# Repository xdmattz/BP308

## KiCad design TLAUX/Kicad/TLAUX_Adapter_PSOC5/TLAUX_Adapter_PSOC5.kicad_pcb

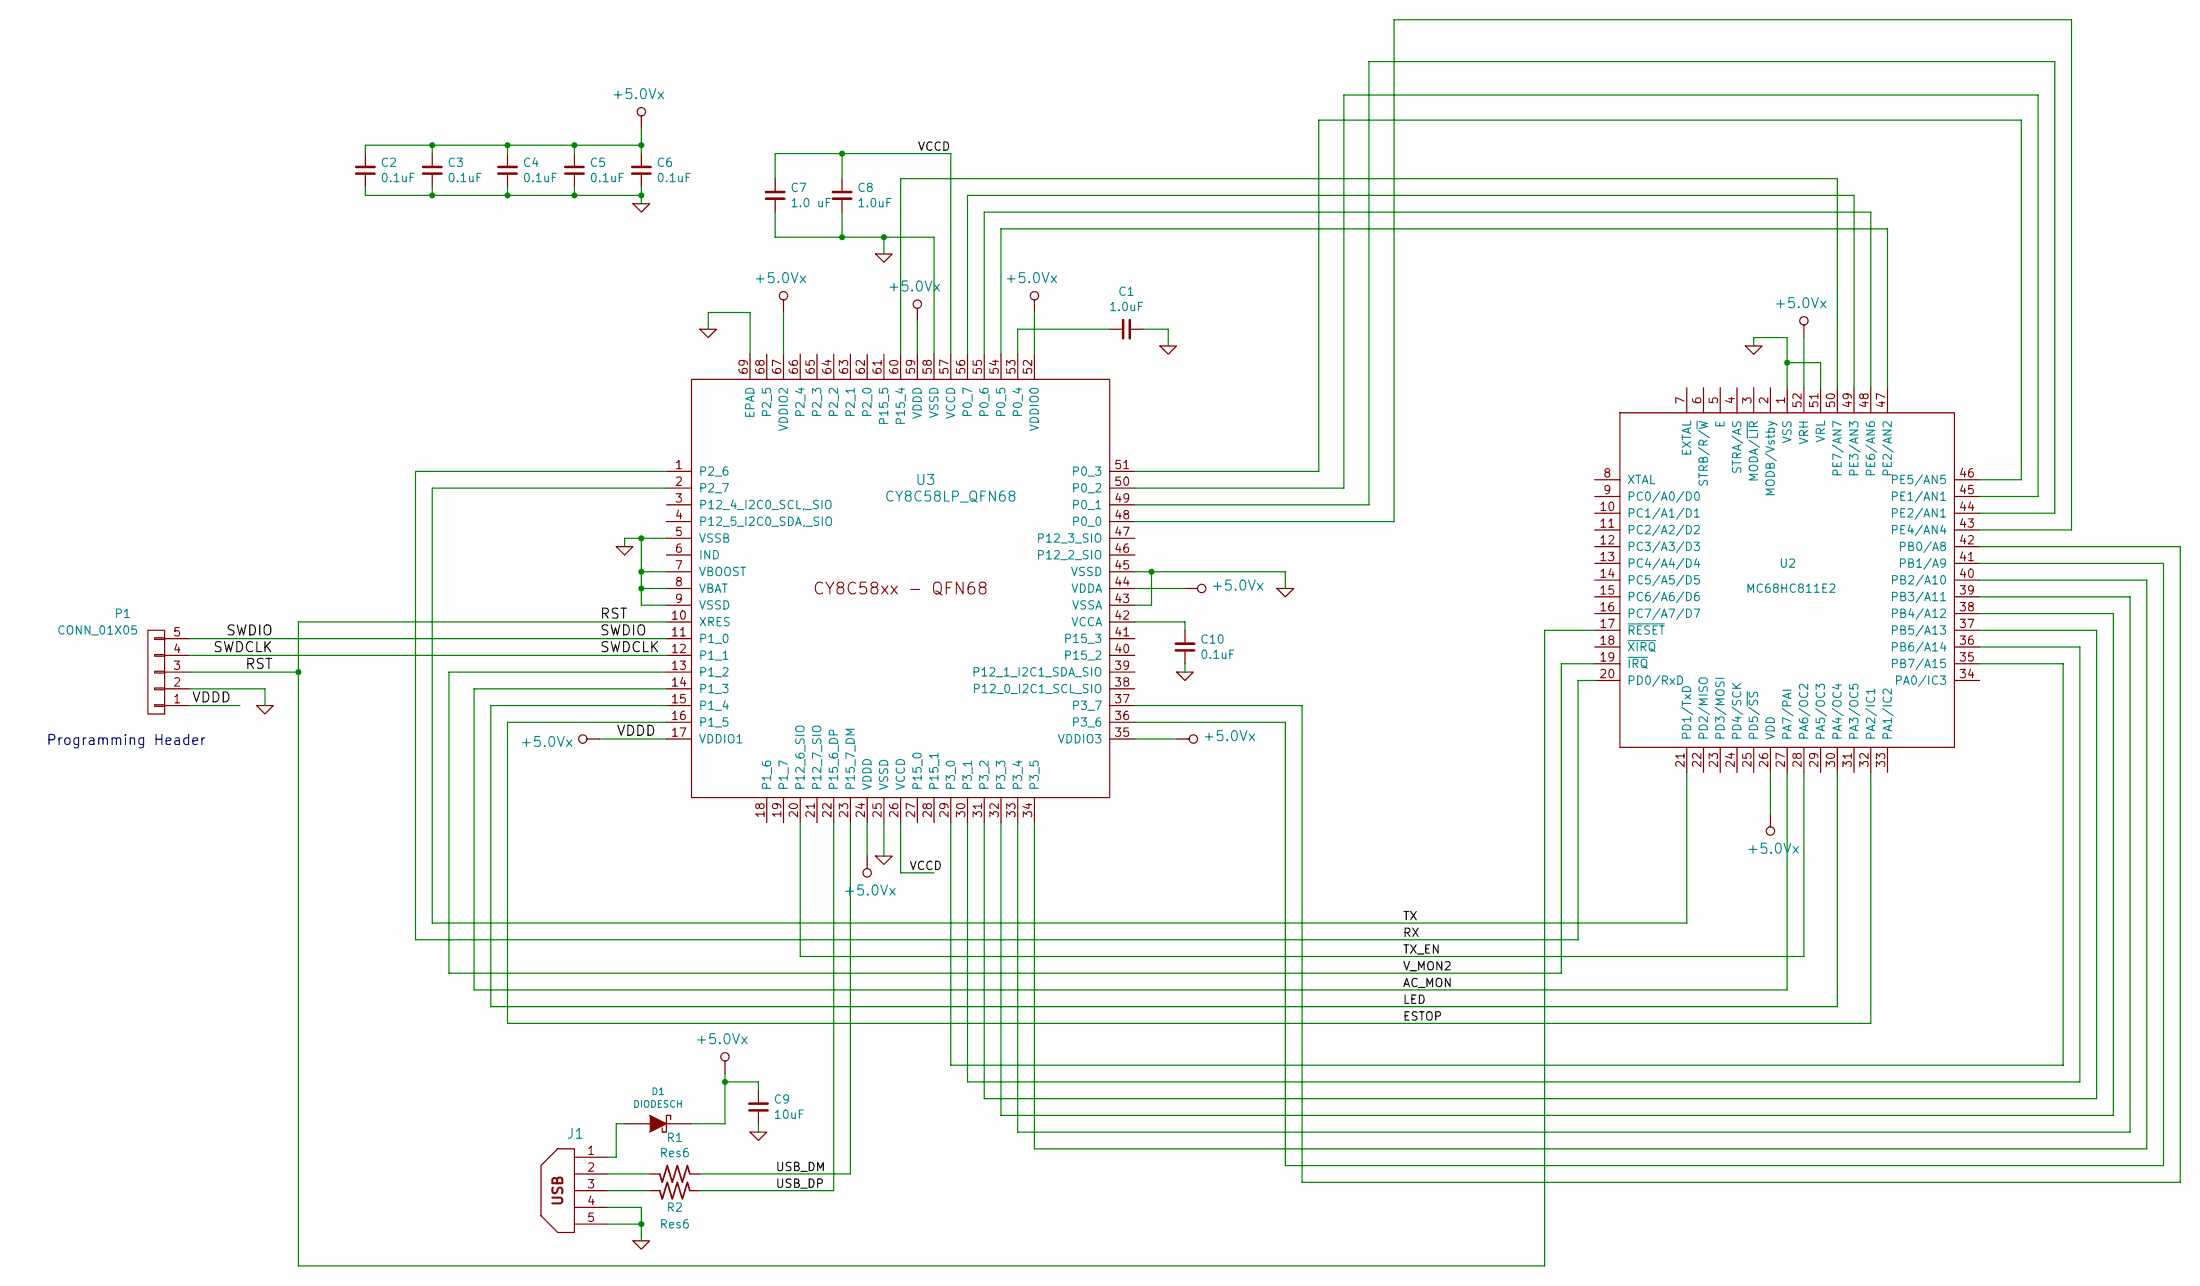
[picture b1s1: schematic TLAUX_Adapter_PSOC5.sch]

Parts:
C1, C8: 1.0uF; cap_0603
C2, C3, C4, C5, C6, C10: 0.1uF; cap_0402
C7: 1.0 uF; cap_0603
C9: 10uF; cap_0805
D1: DIODESCH; SOD-123
J1: USB_micro-B; conn_usb_B_mini_smd
P1: CONN_01X05; pin_strip_5
R1, R2: Res6; res_0603
U2: MC68HC811E2; PLCC_52_Socket
U3: CY8C58LP_QFN68; QFN_68; Digikey 428-3231-ND

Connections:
+5.0Vx: C2.2, C3.2, C4.2, C5.2, C6.2, C9.2, D1.1 (K), P1.1, U2.26 (VDD), U2.52 (VRH), U3.17 (VDDIO1), U3.24 (VDDD), U3.35 (VDDIO3), U3.44 (VDDA), U3.52 (VDDIO0), U3.59 (VDDD), U3.67 (VDDIO2)
/AC_MON: U2.27 (PA7/PAI), U3.14 (P1_3)
/ESTOP: U2.32 (PA2/IC1), U3.16 (P1_5)
/LED: U2.30 (PA4/OC4), U3.15 (P1_4)
/RST: P1.3, U2.17 (~RESET), U3.10 (XRES)
/RX: U2.20 (PD0/RxD), U3.1 (P2_6)
/SWDCLK: P1.4, U3.12 (P1_1)
/SWDIO: P1.5, U3.11 (P1_0)
/TX: U2.21 (PD1/TxD), U3.2 (P2_7)
/TX_EN: U2.28 (PA6/OC2), U3.20 (P12_6_SIO)
/USB_DM: R1.1, U3.23 (P15_7_DM)
/USB_DP: R2.1, U3.22 (P15_6_DP)
/VCCD: C7.2, C8.2, U3.26 (VCCD), U3.57 (VCCD)
/V_MON2: U2.19 (~IRQ), U3.13 (P1_2)
GND: C1.1, C2.1, C3.1, C4.1, C5.1, C6.1, C7.1, C8.1, C9.1, C10.1, J1.4, J1.5, P1.2, U2.1 (VSS), U2.51 (VRL), U3.5 (VSSB), U3.7 (VBOOST), U3.8 (VBAT), U3.9 (VSSD), U3.25 (VSSD), U3.43 (VSSA), U3.45 (VSSD), U3.58 (VSSD), U3.69 (EPAD)
unnamed: C1.2, U3.53 (P0_4)
unnamed: C10.2, U3.42 (VCCA)
unnamed: D1.2 (A), J1.1
unnamed: J1.2, R1.2
unnamed: J1.3, R2.2
unnamed: U2.35 (PB7/A15), U3.29 (P3_0)
unnamed: U2.36 (PB6/A14), U3.30 (P3_1)
unnamed: U2.37 (PB5/A13), U3.31 (P3_2)
unnamed: U2.38 (PB4/A12), U3.32 (P3_3)
unnamed: U2.39 (PB3/A11), U3.33 (P3_4)
unnamed: U2.40 (PB2/A10), U3.34 (P3_5)
unnamed: U2.41 (PB1/A9), U3.36 (P3_6)
unnamed: U2.42 (PB0/A8), U3.37 (P3_7)
unnamed: U2.43 (PE4/AN4), U3.48 (P0_0)
unnamed: U2.44 (PE2/AN1), U3.49 (P0_1)
unnamed: U2.45 (PE1/AN1), U3.50 (P0_2)
unnamed: U2.46 (PE5/AN5), U3.51 (P0_3)
unnamed: U2.47 (PE2/AN2), U3.54 (P0_5)
unnamed: U2.48 (PE6/AN6), U3.55 (P0_6)
unnamed: U2.49 (PE3/AN3), U3.56 (P0_7)
unnamed: U2.50 (PE7/AN7), U3.60 (P15_4)

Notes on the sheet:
Programming Header

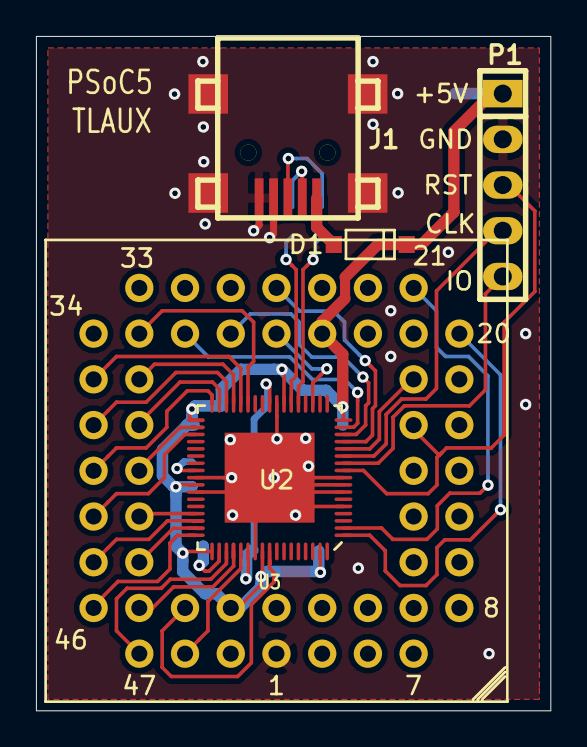
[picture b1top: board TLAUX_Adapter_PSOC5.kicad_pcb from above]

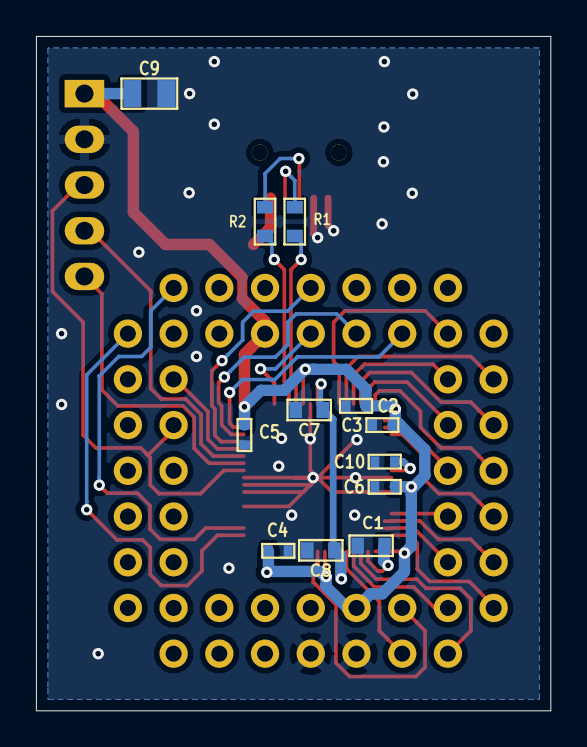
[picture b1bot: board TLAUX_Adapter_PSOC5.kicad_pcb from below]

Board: 2 copper layers, 28.6 x 37.5 mm, 17 parts (12 on the bottom side), 36 nets.

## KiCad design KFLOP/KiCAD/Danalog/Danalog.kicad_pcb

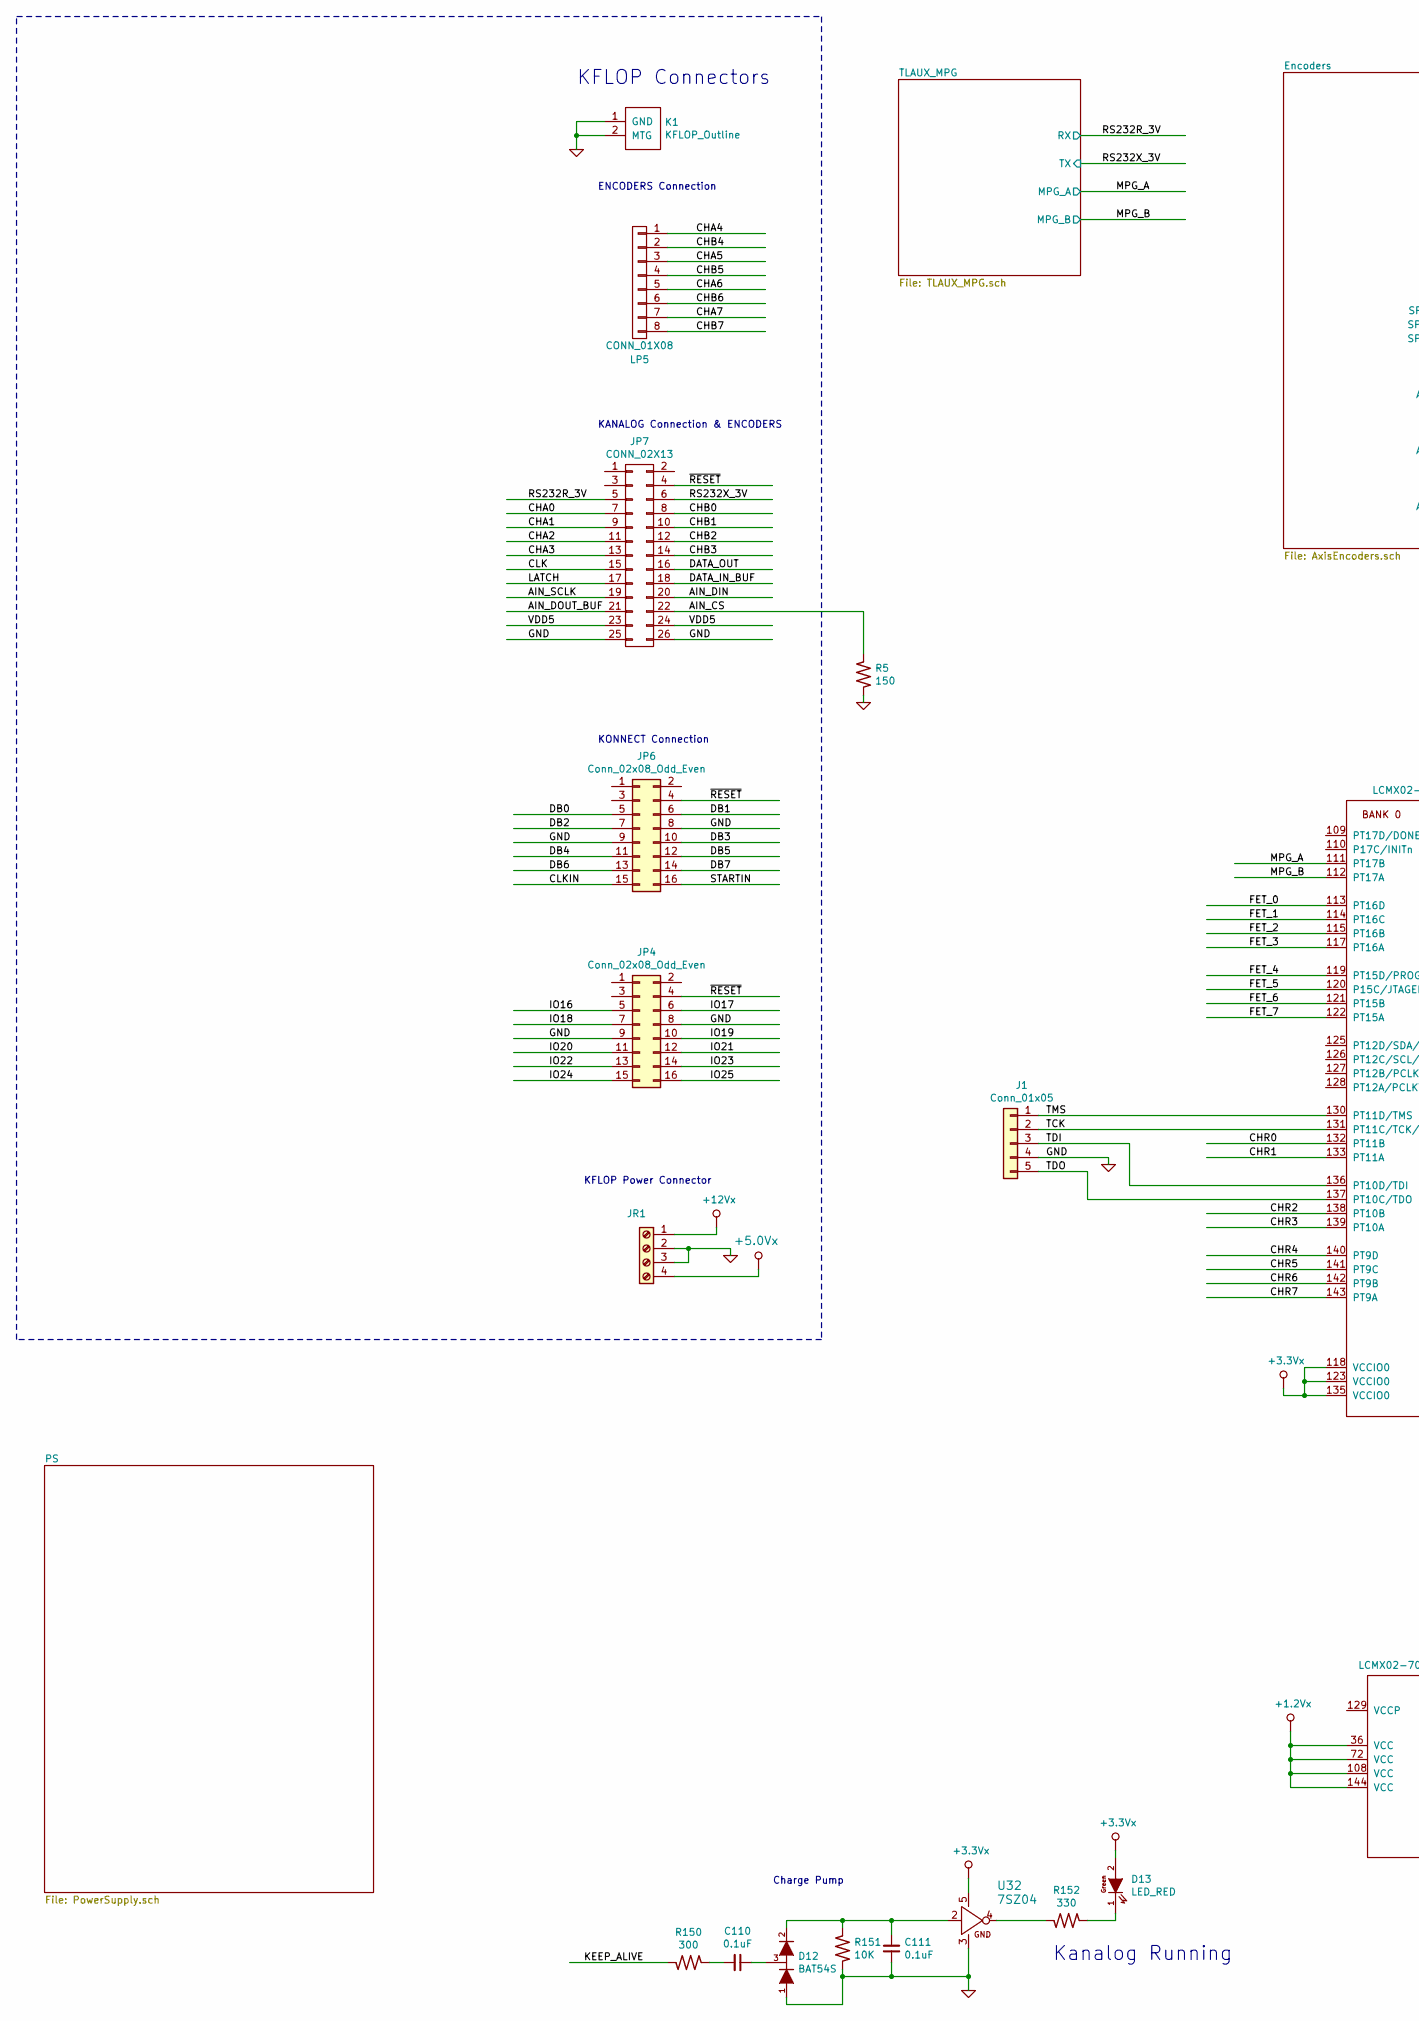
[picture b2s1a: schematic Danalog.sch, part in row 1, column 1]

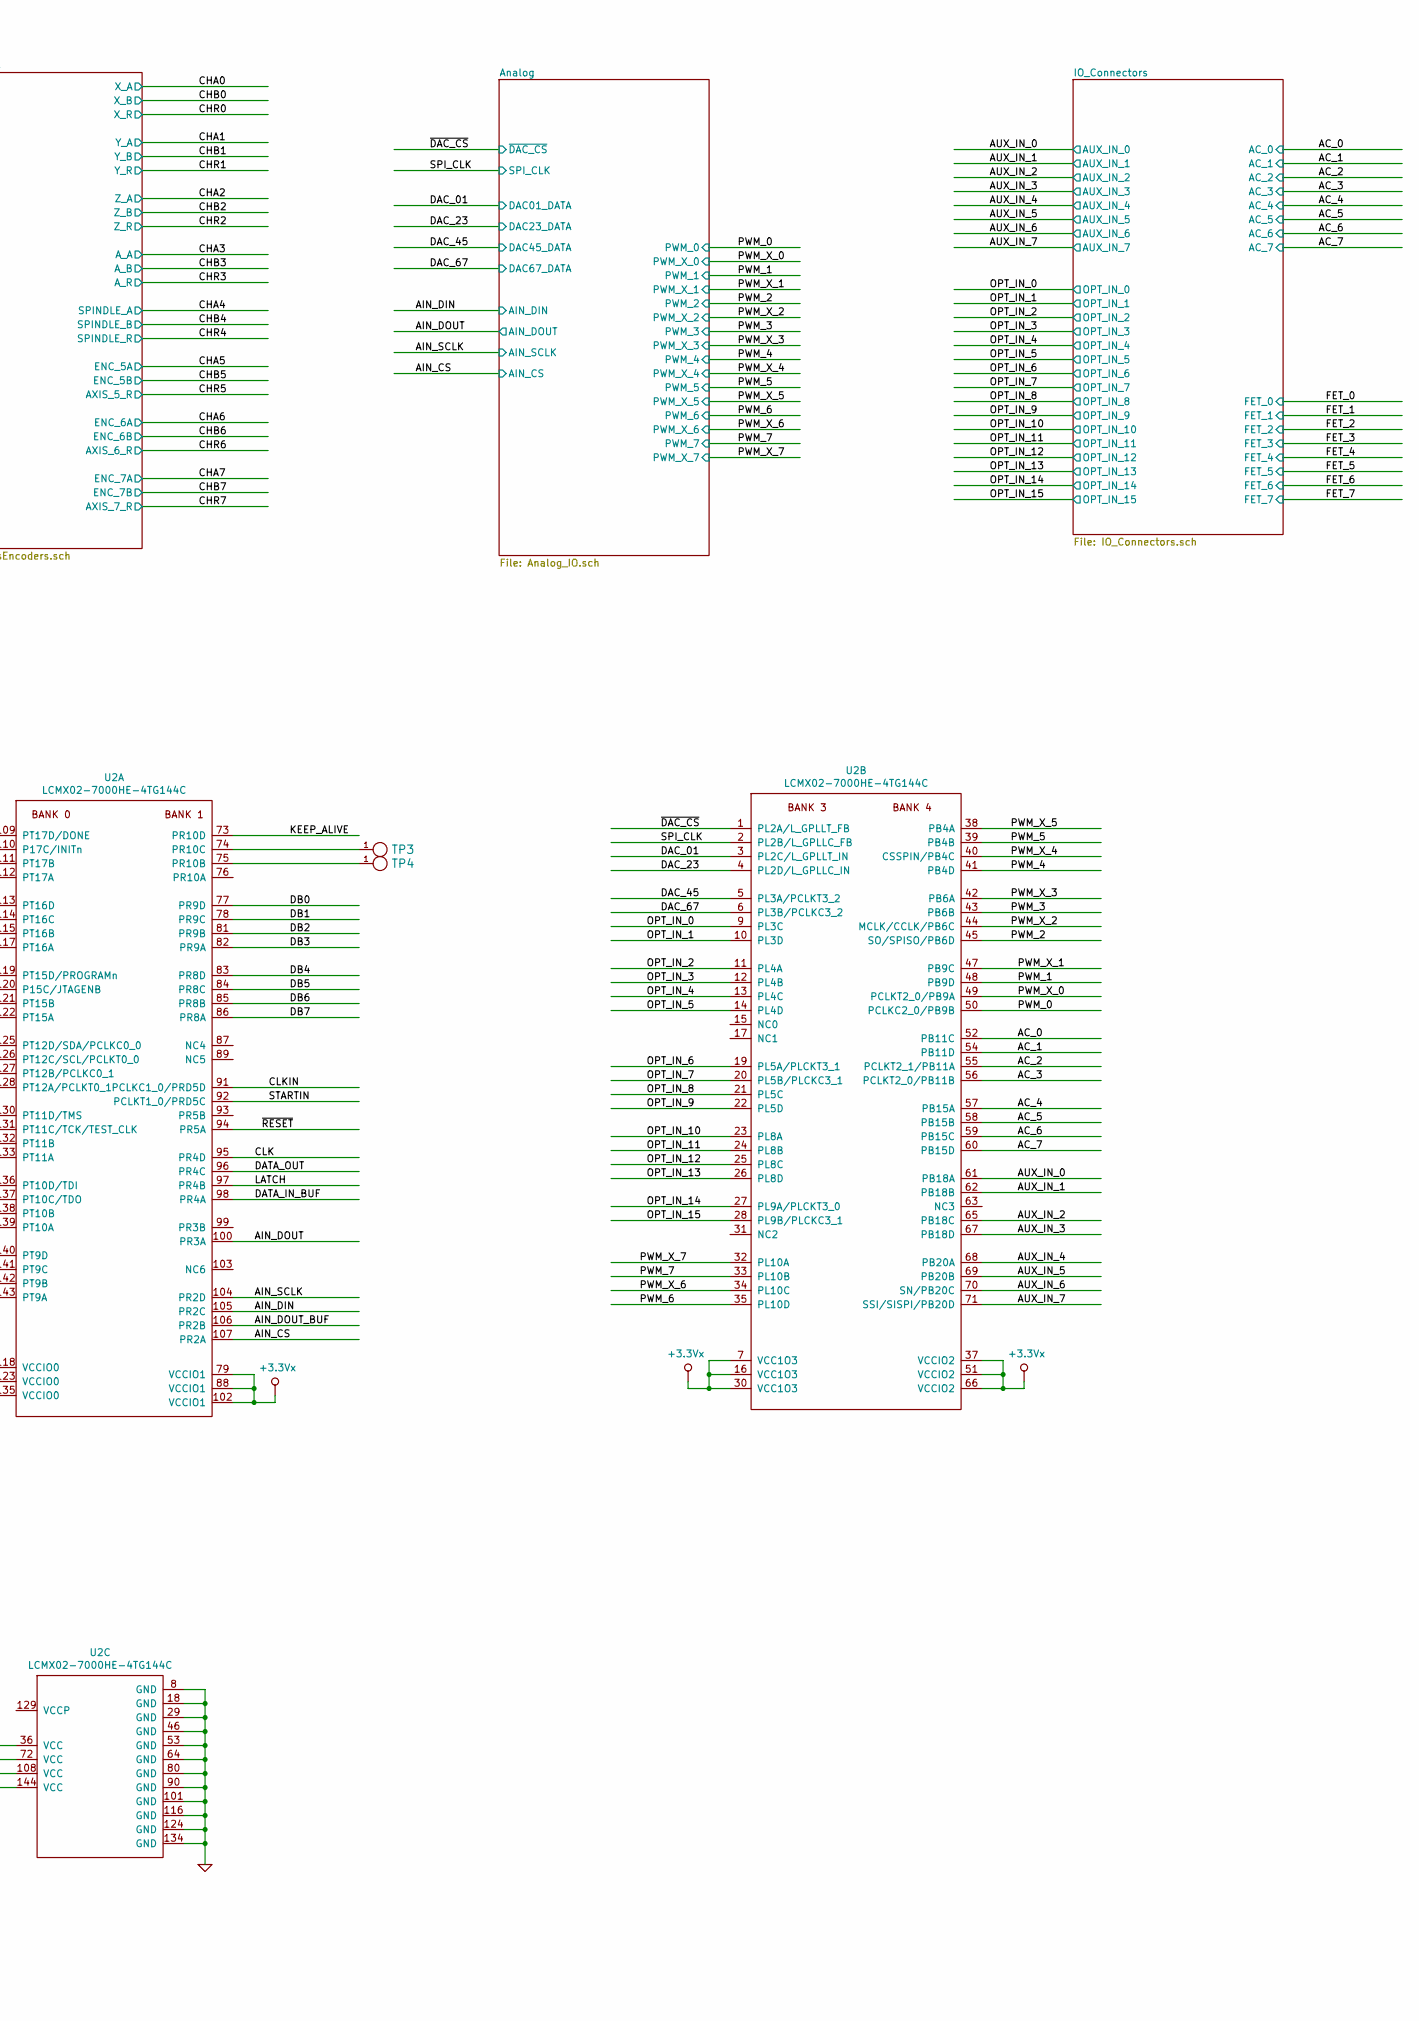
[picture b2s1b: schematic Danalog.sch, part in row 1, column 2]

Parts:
C110, C111: 0.1uF; cap_0603
D12: BAT54S; sot-23
D13: LED_RED; Led_1206_Short
J1: Conn_01x05; Header_5x100
JP4, JP6: Conn_02x08_Odd_Even; vasch_strip_8x2
JP7: CONN_02X13; vasch_strip_13x2
JR1: Screw_Terminal_01x04; Terminal_Block_RA_4_5_08mm
K1: KFLOP_Outline; KFLOP_Mounting
LP5: CONN_01X08; Molex_43860_rj45_no_shield
R5: 150; res_0805
R150: 300; res_0603
R151: 10K; res_0603
R152: 330; res_0603
TP3, TP4: TEST_POINT; TP60
U2: LCMX02-7000HE-4TG144C; QFP-144_20x20_Pitch0.5mm
U32: 7SZ04; sot-23-5

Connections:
+1.2Vx: U2.36 (VCC), U2.72 (VCC), U2.108 (VCC), U2.144 (VCC); also elsewhere on the board
+3.3Vx: D13.2 (A), U2.7 (VCC1O3), U2.16 (VCC1O3), U2.30 (VCC1O3), U2.37 (VCCIO2), U2.51 (VCCIO2), U2.66 (VCCIO2), U2.79 (VCCIO1), U2.88 (VCCIO1), U2.102 (VCCIO1), U2.118 (VCCIO0), U2.123 (VCCIO0), U2.135 (VCCIO0), U32.5 (VCC); also elsewhere on the board
+5.0Vx: JR1.4; also elsewhere on the board
+12Vx: JR1.1; also elsewhere on the board
/AC_0: U2.52 (PB11C); also elsewhere on the board
/AC_1: U2.54 (PB11D); also elsewhere on the board
/AC_2: U2.55 (PCLKT2_1/PB11A); also elsewhere on the board
/AC_3: U2.56 (PCLKT2_0/PB11B); also elsewhere on the board
/AC_4: U2.57 (PB15A); also elsewhere on the board
/AC_5: U2.58 (PB15B); also elsewhere on the board
/AC_6: U2.59 (PB15C); also elsewhere on the board
/AC_7: U2.60 (PB15D); also elsewhere on the board
/AIN_CS: JP7.22, R5.2, U2.107 (PR2A); also elsewhere on the board
/AIN_DIN: JP7.20, U2.105 (PR2C); also elsewhere on the board
/AIN_DOUT: U2.100 (PR3A); also elsewhere on the board
/AIN_DOUT_BUF: JP7.21, U2.106 (PR2B)
/AIN_SCLK: JP7.19, U2.104 (PR2D); also elsewhere on the board
/AUX_IN_0: U2.61 (PB18A); also elsewhere on the board
/AUX_IN_1: U2.62 (PB18B); also elsewhere on the board
/AUX_IN_2: U2.65 (PB18C); also elsewhere on the board
/AUX_IN_3: U2.67 (PB18D); also elsewhere on the board
/AUX_IN_4: U2.68 (PB20A); also elsewhere on the board
/AUX_IN_5: U2.69 (PB20B); also elsewhere on the board
/AUX_IN_6: U2.70 (SN/PB20C); also elsewhere on the board
/AUX_IN_7: U2.71 (SSI/SISPI/PB20D); also elsewhere on the board
/CHA0: JP7.7; also elsewhere on the board
/CHA1: JP7.9; also elsewhere on the board
/CHA2: JP7.11; also elsewhere on the board
/CHA3: JP7.13; also elsewhere on the board
/CHA4: LP5.1; also elsewhere on the board
/CHA5: LP5.3; also elsewhere on the board
/CHA6: LP5.5; also elsewhere on the board
/CHA7: LP5.7; also elsewhere on the board
/CHB0: JP7.8; also elsewhere on the board
/CHB1: JP7.10; also elsewhere on the board
/CHB2: JP7.12; also elsewhere on the board
/CHB3: JP7.14; also elsewhere on the board
/CHB4: LP5.2; also elsewhere on the board
/CHB5: LP5.4; also elsewhere on the board
/CHB6: LP5.6; also elsewhere on the board
/CHB7: LP5.8; also elsewhere on the board
/CHR0: U2.132 (PT11B); also elsewhere on the board
/CHR1: U2.133 (PT11A); also elsewhere on the board
/CHR2: U2.138 (PT10B); also elsewhere on the board
/CHR3: U2.139 (PT10A); also elsewhere on the board
/CHR4: U2.140 (PT9D); also elsewhere on the board
/CHR5: U2.141 (PT9C); also elsewhere on the board
/CHR6: U2.142 (PT9B); also elsewhere on the board
/CHR7: U2.143 (PT9A); also elsewhere on the board
/CLK: JP7.15, U2.95 (PR4D)
/CLKIN: JP6.15, U2.91 (PCLKC1_0/PRD5D)
/DAC_01: U2.3 (PL2C/L_GPLLT_IN); also elsewhere on the board
/DAC_23: U2.4 (PL2D/L_GPLLC_IN); also elsewhere on the board
/DAC_45: U2.5 (PL3A/PCLKT3_2); also elsewhere on the board
/DAC_67: U2.6 (PL3B/PCLKC3_2); also elsewhere on the board
/DATA_IN_BUF: JP7.18, U2.98 (PR4A)
/DATA_OUT: JP7.16, U2.96 (PR4C)
/DB0: JP6.5, U2.77 (PR9D)
/DB1: JP6.6, U2.78 (PR9C)
/DB2: JP6.7, U2.81 (PR9B)
/DB3: JP6.10, U2.82 (PR9A)
/DB4: JP6.11, U2.83 (PR8D)
/DB5: JP6.12, U2.84 (PR8C)
/DB6: JP6.13, U2.85 (PR8B)
/DB7: JP6.14, U2.86 (PR8A)
/FET_0: U2.113 (PT16D); also elsewhere on the board
/FET_1: U2.114 (PT16C); also elsewhere on the board
/FET_2: U2.115 (PT16B); also elsewhere on the board
/FET_3: U2.117 (PT16A); also elsewhere on the board
/FET_4: U2.119 (PT15D/PROGRAMn); also elsewhere on the board
/FET_5: U2.120 (P15C/JTAGENB); also elsewhere on the board
/FET_6: U2.121 (PT15B); also elsewhere on the board
/FET_7: U2.122 (PT15A); also elsewhere on the board
/IO16: JP4.5
/IO17: JP4.6
/IO18: JP4.7
/IO19: JP4.10
/IO20: JP4.11
/IO21: JP4.12
/IO22: JP4.13
/IO23: JP4.14
/IO24: JP4.15
/IO25: JP4.16
/KEEP_ALIVE: R150.1, U2.73 (PR10D)
/LATCH: JP7.17, U2.97 (PR4B)
/MPG_A: U2.111 (PT17B); also elsewhere on the board
/MPG_B: U2.112 (PT17A); also elsewhere on the board
/OPT_IN_0: U2.9 (PL3C); also elsewhere on the board
/OPT_IN_1: U2.10 (PL3D); also elsewhere on the board
/OPT_IN_2: U2.11 (PL4A); also elsewhere on the board
/OPT_IN_3: U2.12 (PL4B); also elsewhere on the board
/OPT_IN_4: U2.13 (PL4C); also elsewhere on the board
/OPT_IN_5: U2.14 (PL4D); also elsewhere on the board
/OPT_IN_6: U2.19 (PL5A/PLCKT3_1); also elsewhere on the board
/OPT_IN_7: U2.20 (PL5B/PLCKC3_1); also elsewhere on the board
/OPT_IN_8: U2.21 (PL5C); also elsewhere on the board
/OPT_IN_9: U2.22 (PL5D); also elsewhere on the board
/OPT_IN_10: U2.23 (PL8A); also elsewhere on the board
/OPT_IN_11: U2.24 (PL8B); also elsewhere on the board
/OPT_IN_12: U2.25 (PL8C); also elsewhere on the board
/OPT_IN_13: U2.26 (PL8D); also elsewhere on the board
/OPT_IN_14: U2.27 (PL9A/PLCKT3_0); also elsewhere on the board
/OPT_IN_15: U2.28 (PL9B/PLCKC3_1); also elsewhere on the board
/PWM_0: U2.50 (PCLKC2_0/PB9B); also elsewhere on the board
/PWM_1: U2.48 (PB9D); also elsewhere on the board
/PWM_2: U2.45 (SO/SPISO/PB6D); also elsewhere on the board
/PWM_3: U2.43 (PB6B); also elsewhere on the board
/PWM_4: U2.41 (PB4D); also elsewhere on the board
/PWM_5: U2.39 (PB4B); also elsewhere on the board
/PWM_6: U2.35 (PL10D); also elsewhere on the board
/PWM_7: U2.33 (PL10B); also elsewhere on the board
/PWM_X_0: U2.49 (PCLKT2_0/PB9A); also elsewhere on the board
/PWM_X_1: U2.47 (PB9C); also elsewhere on the board
/PWM_X_2: U2.44 (MCLK/CCLK/PB6C); also elsewhere on the board
/PWM_X_3: U2.42 (PB6A); also elsewhere on the board
/PWM_X_4: U2.40 (CSSPIN/PB4C); also elsewhere on the board
/PWM_X_5: U2.38 (PB4A); also elsewhere on the board
/PWM_X_6: U2.34 (PL10C); also elsewhere on the board
/PWM_X_7: U2.32 (PL10A); also elsewhere on the board
/RS232R_3V: JP7.5; also elsewhere on the board
/RS232X_3V: JP7.6; also elsewhere on the board
/SPI_CLK: U2.2 (PL2B/L_GPLLC_FB); also elsewhere on the board
/STARTIN: JP6.16, U2.92 (PCLKT1_0/PRD5C)
/TCK: J1.2, U2.131 (PT11C/TCK/TEST_CLK)
/TDI: J1.3, U2.136 (PT10D/TDI)
/TDO: J1.5, U2.137 (PT10C/TDO)
/TMS: J1.1, U2.130 (PT11D/TMS)
/VDD5: JP7.23, JP7.24
/~DAC_CS: U2.1 (PL2A/L_GPLLT_FB); also elsewhere on the board
/~RESET: JP4.4, JP6.4, JP7.4, U2.94 (PR5A)
GND: C111.2, D12.1 (A1), J1.4, JP4.8, JP4.9, JP6.8, JP6.9, JP7.25, JP7.26, JR1.2, JR1.3, K1.1 (GND), K1.2 (MTG), R5.1, R151.2, U2.8 (GND), U2.18 (GND), U2.29 (GND), U2.46 (GND), U2.53 (GND), U2.64 (GND), U2.80 (GND), U2.90 (GND), U2.101 (GND), U2.116 (GND), U2.124 (GND), U2.134 (GND), U32.3 (GND); also elsewhere on the board
unnamed: C110.1, R150.2
unnamed: C110.2, D12.3 (KA)
unnamed: C111.1, D12.2 (K2), R151.1, U32.2 (A)
unnamed: D13.1 (K), R152.1
unnamed: R152.2, U32.4 (Y)
unnamed: TP3.1, U2.74 (PR10C)
unnamed: TP4.1, U2.75 (PR10B)

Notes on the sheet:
KANALOG Connection & ENCODERS
KONNECT Connection
ENCODERS Connection
KFLOP Connectors
KFLOP Power Connector
Kanalog Running
Charge Pump

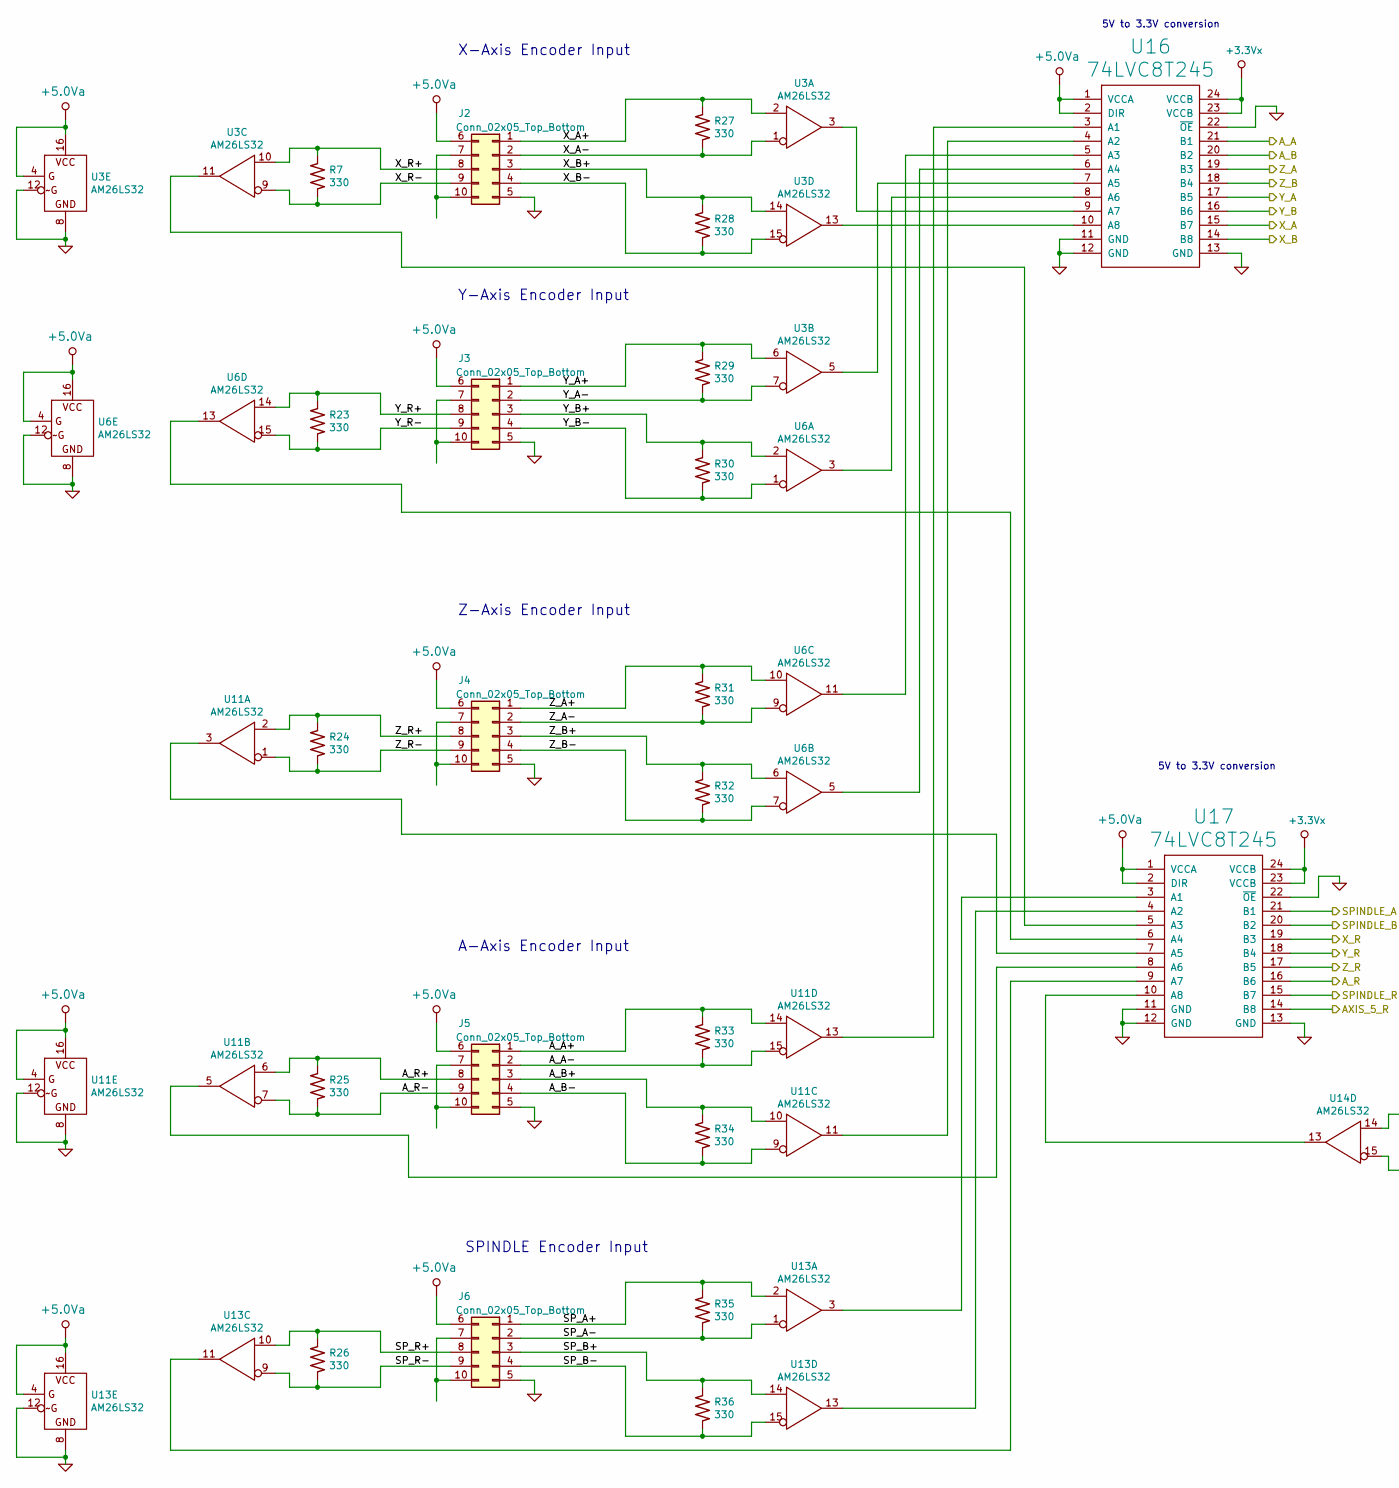
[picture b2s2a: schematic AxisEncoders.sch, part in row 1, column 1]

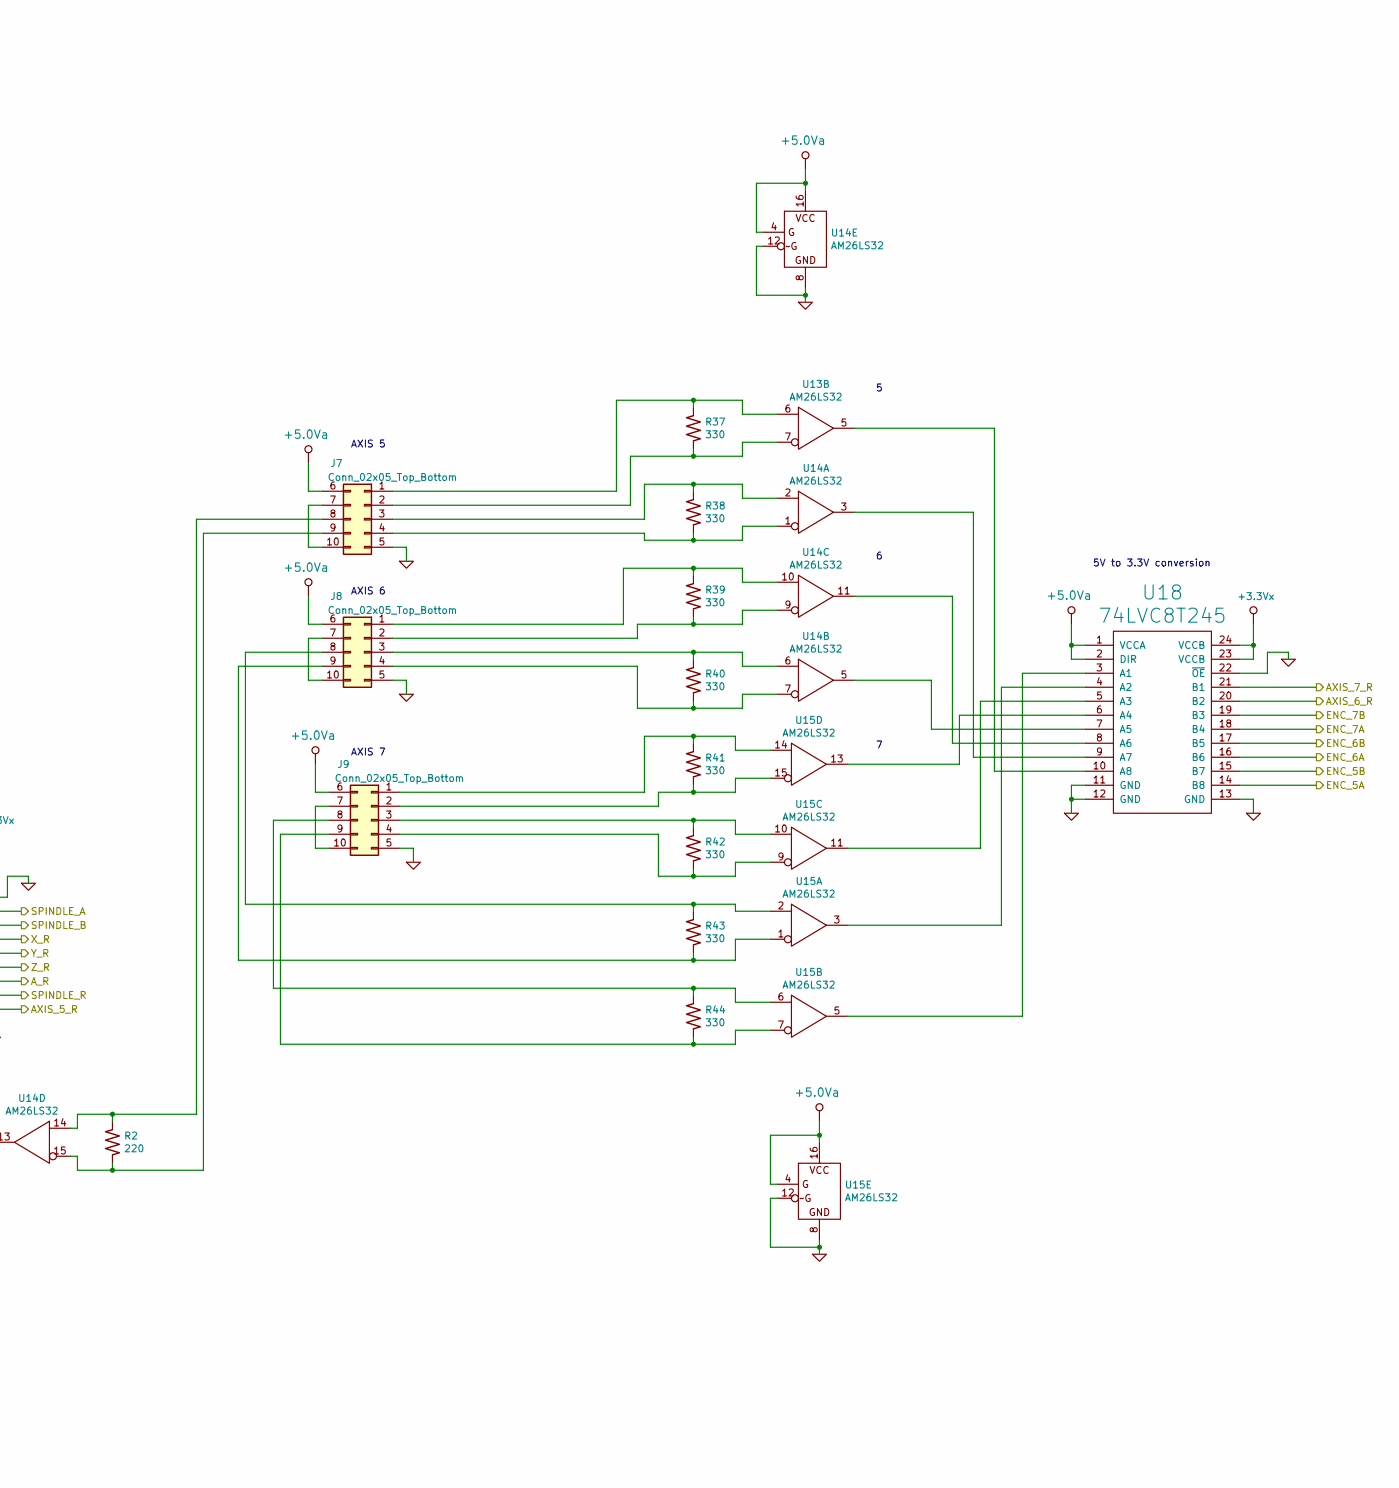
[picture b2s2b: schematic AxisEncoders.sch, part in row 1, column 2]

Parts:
J2, J3, J4, J5, J6, J7, J8, J9: Conn_02x05_Top_Bottom; c-5-103168-3
R2: 220; res_0603
R7, R23, R24, R25, R26, R27, R28, R29, R30, R31, R32, R33, R34, R35, R36, R37, R38, R39, R40, R41, R42, R43, R44: 330; res_0603
U3, U6, U11, U13, U14, U15: AM26LS32; SOIC-16_3.9x9.9mm_Pitch1.27mm
U16, U17, U18: 74LVC8T245; SSOP-24_5.3x8.2mm_Pitch0.65mm

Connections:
+3.3Vx: U16.23 (VCCB), U16.24 (VCCB), U17.23 (VCCB), U17.24 (VCCB), U18.23 (VCCB), U18.24 (VCCB); also elsewhere on the board
+5.0Va: J2.6, J3.6, J4.6, J5.6, J6.6, J7.6, J8.6, J9.6, U3.4 (G), U3.16 (VCC), U6.4 (G), U6.16 (VCC), U11.4 (G), U11.16 (VCC), U13.4 (G), U13.16 (VCC), U14.4 (G), U14.16 (VCC), U15.4 (G), U15.16 (VCC), U16.1 (VCCA), U16.2 (DIR), U17.1 (VCCA), U17.2 (DIR), U18.1 (VCCA), U18.2 (DIR); also elsewhere on the board
/CHA0: U16.15 (B7); also elsewhere on the board
/CHA1: U16.17 (B5); also elsewhere on the board
/CHA2: U16.19 (B3); also elsewhere on the board
/CHA3: U16.21 (B1); also elsewhere on the board
/CHA4: U17.21 (B1); also elsewhere on the board
/CHA5: U18.14 (B8); also elsewhere on the board
/CHA6: U18.16 (B6); also elsewhere on the board
/CHA7: U18.18 (B4); also elsewhere on the board
/CHB0: U16.14 (B8); also elsewhere on the board
/CHB1: U16.16 (B6); also elsewhere on the board
/CHB2: U16.18 (B4); also elsewhere on the board
/CHB3: U16.20 (B2); also elsewhere on the board
/CHB4: U17.20 (B2); also elsewhere on the board
/CHB5: U18.15 (B7); also elsewhere on the board
/CHB6: U18.17 (B5); also elsewhere on the board
/CHB7: U18.19 (B3); also elsewhere on the board
/CHR0: U17.19 (B3); also elsewhere on the board
/CHR1: U17.18 (B4); also elsewhere on the board
/CHR2: U17.17 (B5); also elsewhere on the board
/CHR3: U17.16 (B6); also elsewhere on the board
/CHR4: U17.15 (B7); also elsewhere on the board
/CHR5: U17.14 (B8); also elsewhere on the board
/CHR6: U18.20 (B2); also elsewhere on the board
/CHR7: U18.21 (B1); also elsewhere on the board
/Encoders/A_A+: J5.1, R33.1, U11.14 (4A)
/Encoders/A_A-: J5.2, R33.2, U11.15 (4B)
/Encoders/A_B+: J5.3, R34.1, U11.10 (3A)
/Encoders/A_B-: J5.4, R34.2, U11.9 (3B)
/Encoders/A_R+: J5.8, R25.1, U11.6 (2A)
/Encoders/A_R-: J5.9, R25.2, U11.7 (2B)
/Encoders/SP_A+: J6.1, R35.1, U13.2 (1A)
/Encoders/SP_A-: J6.2, R35.2, U13.1 (1B)
/Encoders/SP_B+: J6.3, R36.1, U13.14 (4A)
/Encoders/SP_B-: J6.4, R36.2, U13.15 (4B)
/Encoders/SP_R+: J6.8, R26.1, U13.10 (3A)
/Encoders/SP_R-: J6.9, R26.2, U13.9 (3B)
/Encoders/X_A+: J2.1, R27.1, U3.2 (1A)
/Encoders/X_A-: J2.2, R27.2, U3.1 (1B)
/Encoders/X_B+: J2.3, R28.1, U3.14 (4A)
/Encoders/X_B-: J2.4, R28.2, U3.15 (4B)
/Encoders/X_R+: J2.8, R7.1, U3.10 (3A)
/Encoders/X_R-: J2.9, R7.2, U3.9 (3B)
/Encoders/Y_A+: J3.1, R29.1, U3.6 (2A)
/Encoders/Y_A-: J3.2, R29.2, U3.7 (2B)
/Encoders/Y_B+: J3.3, R30.1, U6.2 (1A)
/Encoders/Y_B-: J3.4, R30.2, U6.1 (1B)
/Encoders/Y_R+: J3.8, R23.1, U6.14 (4A)
/Encoders/Y_R-: J3.9, R23.2, U6.15 (4B)
/Encoders/Z_A+: J4.1, R31.1, U6.10 (3A)
/Encoders/Z_A-: J4.2, R31.2, U6.9 (3B)
/Encoders/Z_B+: J4.3, R32.1, U6.6 (2A)
/Encoders/Z_B-: J4.4, R32.2, U6.7 (2B)
/Encoders/Z_R+: J4.8, R24.1, U11.2 (1A)
/Encoders/Z_R-: J4.9, R24.2, U11.1 (1B)
GND: J2.5, J3.5, J4.5, J5.5, J6.5, J7.5, J8.5, J9.5, U3.8 (GND), U3.12 (~G), U6.8 (GND), U6.12 (~G), U11.8 (GND), U11.12 (~G), U13.8 (GND), U13.12 (~G), U14.8 (GND), U14.12 (~G), U15.8 (GND), U15.12 (~G), U16.11 (GND), U16.12 (GND), U16.13 (GND), U16.22 (~OE), U17.11 (GND), U17.12 (GND), U17.13 (GND), U17.22 (~OE), U18.11 (GND), U18.12 (GND), U18.13 (GND), U18.22 (~OE); also elsewhere on the board
unnamed: J2.7, J2.10
unnamed: J3.7, J3.10
unnamed: J4.7, J4.10
unnamed: J5.7, J5.10
unnamed: J6.7, J6.10
unnamed: J7.1, R37.1, U13.6 (2A)
unnamed: J7.2, R37.2, U13.7 (2B)
unnamed: J7.3, R38.1, U14.2 (1A)
unnamed: J7.4, R38.2, U14.1 (1B)
unnamed: J7.8, R2.1, U14.14 (4A)
unnamed: J7.9, R2.2, U14.15 (4B)
unnamed: J7.7, J7.10
unnamed: J8.1, R39.1, U14.10 (3A)
unnamed: J8.2, R39.2, U14.9 (3B)
unnamed: J8.3, R40.1, U14.6 (2A)
unnamed: J8.4, R40.2, U14.7 (2B)
unnamed: J8.8, R43.1, U15.2 (1A)
unnamed: J8.9, R43.2, U15.1 (1B)
unnamed: J8.7, J8.10
unnamed: J9.1, R41.1, U15.14 (4A)
unnamed: J9.2, R41.2, U15.15 (4B)
unnamed: J9.3, R42.1, U15.10 (3A)
unnamed: J9.4, R42.2, U15.9 (3B)
unnamed: J9.8, R44.1, U15.6 (2A)
unnamed: J9.9, R44.2, U15.7 (2B)
unnamed: J9.7, J9.10
unnamed: U11.3 (1Y), U17.7 (A5)
unnamed: U11.5 (2Y), U17.8 (A6)
unnamed: U11.11 (3Y), U16.4 (A2)
unnamed: U11.13 (4Y), U16.3 (A1)
unnamed: U13.3 (1Y), U17.3 (A1)
unnamed: U13.5 (2Y), U18.10 (A8)
unnamed: U13.11 (3Y), U17.9 (A7)
unnamed: U13.13 (4Y), U17.4 (A2)
unnamed: U14.3 (1Y), U18.9 (A7)
unnamed: U14.5 (2Y), U18.7 (A5)
unnamed: U14.11 (3Y), U18.8 (A6)
unnamed: U14.13 (4Y), U17.10 (A8)
unnamed: U15.3 (1Y), U18.4 (A2)
unnamed: U15.5 (2Y), U18.3 (A1)
unnamed: U15.11 (3Y), U18.5 (A3)
unnamed: U15.13 (4Y), U18.6 (A4)
unnamed: U6.11 (3Y), U16.5 (A3)
unnamed: U6.5 (2Y), U16.6 (A4)
unnamed: U3.5 (2Y), U16.7 (A5)
unnamed: U6.3 (1Y), U16.8 (A6)
unnamed: U3.3 (1Y), U16.9 (A7)
unnamed: U3.13 (4Y), U16.10 (A8)
unnamed: U3.11 (3Y), U17.5 (A3)
unnamed: U6.13 (4Y), U17.6 (A4)

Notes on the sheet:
X-Axis Encoder Input
Y-Axis Encoder Input
Z-Axis Encoder Input
A-Axis Encoder Input
SPINDLE Encoder Input
5V to 3.3V conversion
AXIS 5
AXIS 6
AXIS 7
